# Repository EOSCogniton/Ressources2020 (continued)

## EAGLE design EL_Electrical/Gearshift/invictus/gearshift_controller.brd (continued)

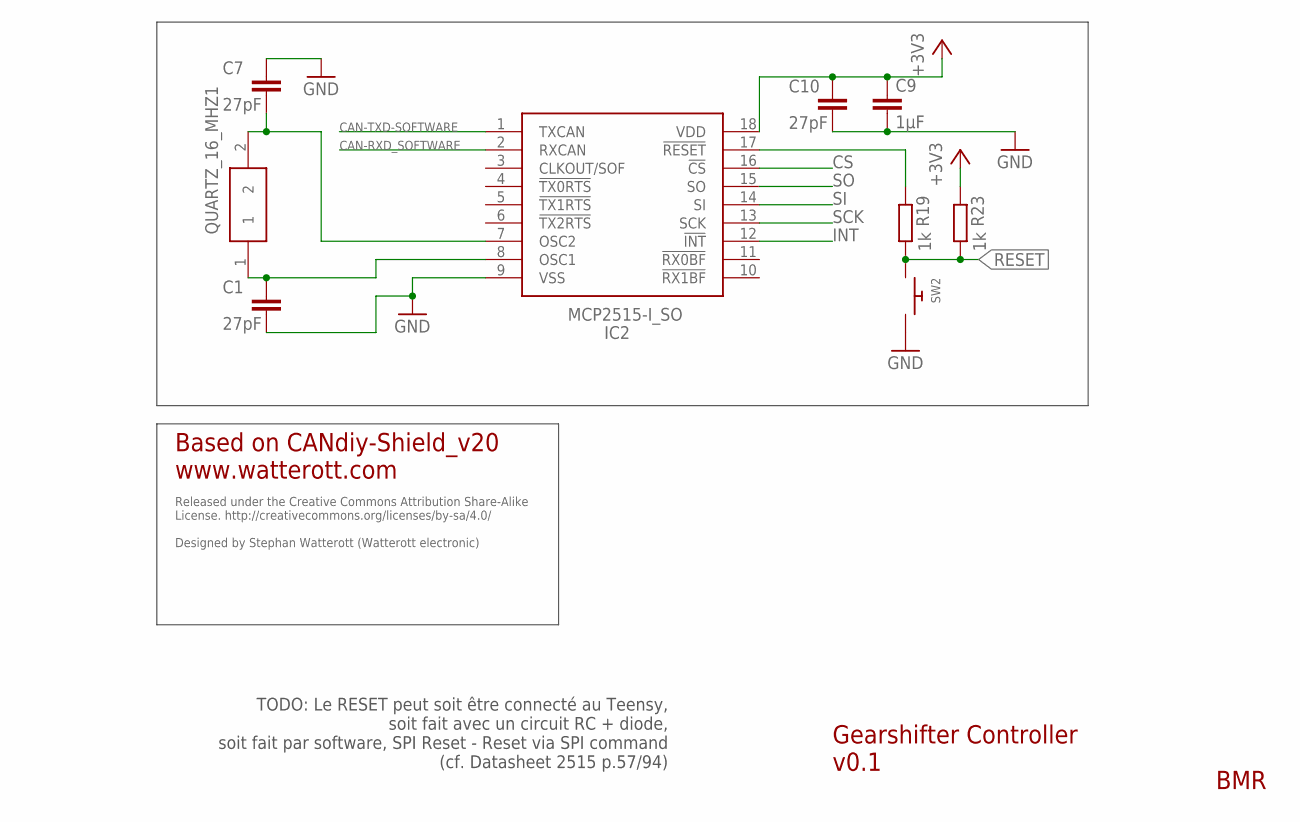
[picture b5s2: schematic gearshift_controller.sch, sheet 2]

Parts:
C1, C7, C10: 27pF; C0805
C9: 1µF; C0805
IC2: MCP2515-I_SO; SOIC127P1030X265-18N
QUARTZ_16_MHZ1: FOXSLF_160-20; HC49SLF_1
R19, R23: 1k; R0805
SW2: SWITCH_PUSHBUTTONEVQ-PE; TACT_PANA-EVQ

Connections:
+3V3: C9.1, C10.1, IC2.18 (VDD), R23.1; also elsewhere on the board
CAN-RXD_SOFTWARE: IC2.2 (RXCAN); also elsewhere on the board
CAN-TXD-SOFTWARE: IC2.1 (TXCAN); also elsewhere on the board
CS: IC2.16 (!CS); also elsewhere on the board
GND: C1.2, C7.1, C9.2, C10.2, IC2.9 (VSS), SW2.P$2; also elsewhere on the board
INT: IC2.12 (!INT); also elsewhere on the board
unnamed: C1.1, IC2.8 (OSC1), QUARTZ_16_MHZ1.1
unnamed: C7.2, IC2.7 (OSC2), QUARTZ_16_MHZ1.2
unnamed: IC2.17 (!RESET), R19.1
RESET: R19.2, R23.2, SW2.P$1
SCK: IC2.13 (SCK); also elsewhere on the board
SI: IC2.14 (SI); also elsewhere on the board
SO: IC2.15 (SO); also elsewhere on the board

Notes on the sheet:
Gearshifter Controller v0.1
BMR
Released under the Creative Commons Attribution Share-Alike License. http://creativecommons.org/licenses/by-sa/4.0/ Designed by Stephan Watterott (Watterott electronic)
Based on CANdiy-Shield_v20 www.watterott.com
TODO: Le RESET peut soit être connecté au Teensy, soit fait avec un circuit RC + diode, soit fait par software, SPI Reset - Reset via SPI command (cf. Datasheet 2515 p.57/94)

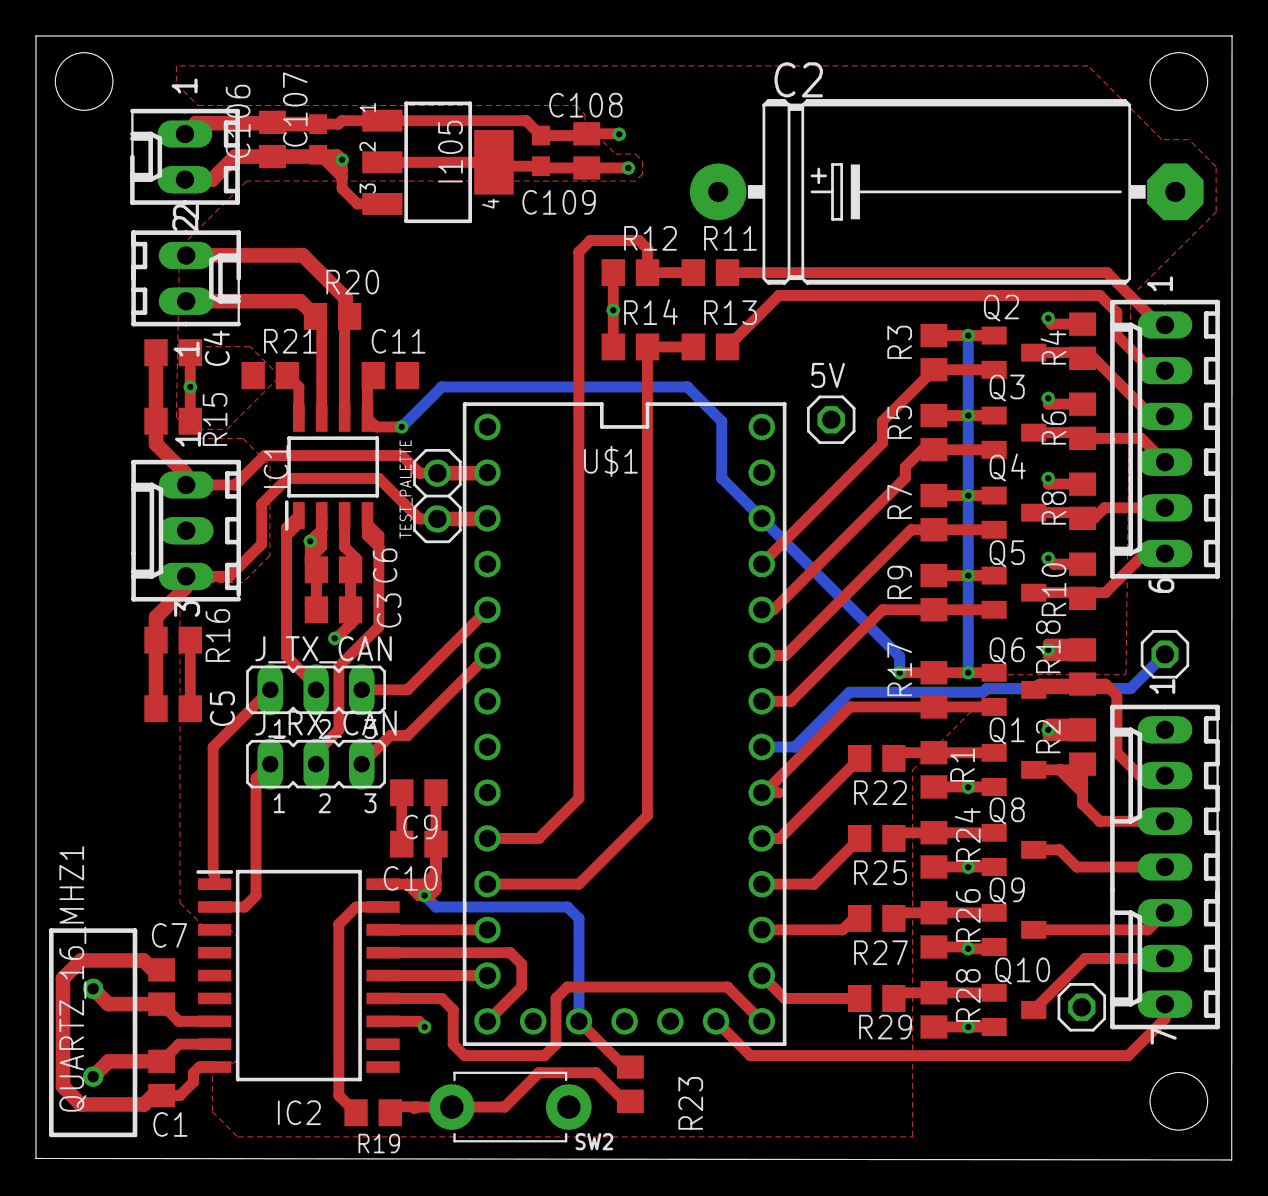
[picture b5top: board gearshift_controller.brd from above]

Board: 4 copper layers, 66.4 x 62.4 mm, 69 parts (0 on the bottom side), 52 nets.

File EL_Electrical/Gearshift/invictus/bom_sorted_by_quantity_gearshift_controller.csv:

"Qty";"Value";"Device";"Package";"Parts";"Description";"ALLIED_NUMBER";"CASE";"DESCRIPTION";"HEIGHT";"MANUFACTURER_NAME";"MANUFACTURER_PART_NUMBER";"MF";"MONTHLY_USAGE";"MPN";"OC_FARNELL";"OC_NEWARK";"PART_NUMBER";"POPULARITY";"PRICE";"RS_PART_NUMBER";"SPICEPREFIX";"SUPPLIER";"TYPE";"VALUE";
"2";"";"JP2E";"JP2";"JP1, JP2";"JUMPER";"";"";"";"";"";"";"";"";"";"";"";"";"34";"";"";"";"";"";"";
"1";"";"SWITCH_PUSHBUTTONEVQ-PE";"TACT_PANA-EVQ";"SW2";"Buttons";"";"";"";"";"";"";"";"";"";"";"";"";"";"";"";"";"";"";"";
"1";"0.1 µF";"C-EUC0805";"C0805";"C11";"CAPACITOR, European symbol";"";"";"";"";"";"";"";"";"";"";"";"";"88";"";"";"C";"";"";"";
"2";"0.33µF";"C-EUC0805";"C0805";"C4, C5";"CAPACITOR, European symbol";"";"";"";"";"";"";"";"";"";"";"";"";"88";"";"";"C";"";"";"";
"1";"1 µF";"C-EUC0805";"C0805";"C3";"CAPACITOR, European symbol";"";"";"";"";"";"";"";"";"";"";"";"";"88";"";"";"C";"";"";"";
"1";"100k";"R-EU_R0805";"R0805";"R21";"RESISTOR, European symbol";"";"";"";"";"";"";"";"";"";"";"";"";"86";"";"";"R";"";"";"";
"2";"100n";"C-EUC0603";"C0603";"C107, C109";"CAPACITOR, European symbol";"";"";"";"";"";"";"";"";"";"";"";"";"";"";"";"";"";"";"";
"16";"10k";"R-EU_R0805";"R0805";"R1, R3, R4, R5, R6, R7, R8, R9, R10, R15, R16, R17, R18, R24, R26, R28";"RESISTOR, European symbol";"";"";"";"";"";"";"";"";"";"";"";"";"86";"";"";"R";"";"";"";
"2";"10µ";"C-EUC0805";"C0805";"C106, C108";"CAPACITOR, European symbol";"";"";"";"";"";"";"";"";"";"";"";"";"88";"";"";"C";"";"";"";
"1";"120 ";"R-EU_R0805";"R0805";"R20";"RESISTOR, European symbol";"";"";"";"";"";"";"";"";"";"";"";"";"86";"";"";"R";"";"";"";
"2";"18k";"R-EU_R0805";"R0805";"R11, R13";"RESISTOR, European symbol";"";"";"";"";"";"";"";"";"";"";"";"";"86";"";"";"R";"";"";"";
"2";"1k";"R-EU_R0805";"R0805";"R19, R23";"RESISTOR, European symbol";"";"";"";"";"";"";"";"";"";"";"";"";"86";"";"";"R";"";"";"";
"1";"1µF";"C-EUC0805";"C0805";"C9";"CAPACITOR, European symbol";"";"";"";"";"";"";"";"";"";"";"";"";"88";"";"";"C";"";"";"";
"1";"22-05-7028-02";"22-05-7028-02";"7395-02";"ALIM";"CONNECTOR";"";"";"";"";"";"";"";"";"";"";"";"";"";"";"";"";"";"";"";
"1";"22-05-7028-02";"22-05-7028-02";"7395-02";"CONN_CAN";"CONNECTOR";"";"";"";"";"";"";"MOLEX";"";"";"9731601";"unknown";"";"0";"";"";"";"";"";"";
"1";"22-05-7038-03";"22-05-7038-03";"7395-03";"PALETTE";"CONNECTOR";"";"";"";"";"";"";"";"";"";"";"";"";"";"";"";"";"";"";"";
"1";"22-05-7068-06";"22-05-7068-06";"7395-06";"CONN_MOTOR";"CONNECTOR";"";"";"";"";"";"";"MOLEX";"";"";"unknown";"unknown";"";"0";"";"";"";"";"";"";
"1";"22-05-7078-07";"22-05-7078-07";"7395-07";"CONN_DTA";"CONNECTOR";"";"";"";"";"";"";"MOLEX";"";"";"unknown";"unknown";"";"0";"";"";"";"";"";"";
"4";"27pF";"C-EUC0805";"C0805";"C1, C6, C7, C10";"CAPACITOR, European symbol";"";"";"";"";"";"";"";"";"";"";"";"";"88";"";"";"C";"";"";"";
"4";"330";"R-EU_R0805";"R0805";"R22, R25, R27, R29";"RESISTOR, European symbol";"";"";"";"";"";"";"";"";"";"";"";"";"86";"";"";"R";"";"";"";
"1";"4k7";"R-EU_R0805";"R0805";"R2";"RESISTOR, European symbol";"";"";"";"";"";"";"";"";"";"";"";"";"86";"";"";"R";"";"";"";
"2";"6k8";"R-EU_R0805";"R0805";"R12, R14";"RESISTOR, European symbol";"";"";"";"";"";"";"";"";"";"";"";"";"86";"";"";"R";"";"";"";
"9";"BSS138";"BSS123";"SOT23";"Q1, Q2, Q3, Q4, Q5, Q6, Q8, Q9, Q10";"N-CHANNEL MOS FET";"";"";"";"";"";"";"";"";"";"";"";"";"21";"";"";"";"";"";"";
"1";"FOXSLF_160-20";"FOXSLF_160-20";"HC49SLF_1";"QUARTZ_16_MHZ1";"Crystal 16.000MHz HC49S HC-49-SLF Crystal 16MHz, ??30ppm, 2-Pin";"";"";"Crystal 16.000MHz HC49S HC-49-SLF Crystal 16MHz, ??30ppm, 2-Pin";"mm";"Fox";"FOXSLF/160-20";"";"";"";"";"";"";"";"";"1734298";"";"";"";"";
"1";"LM1117MPX-5.0";"0022_LM1117IMPX-5.0";"LINEAR_SOT223";"I105";"Low-dropout linear regulator 5V  -LM1117IMPX-5.0";"";"SOT223";"";"";"";"";"";"_____";"";"";"";"LM1117IMPX-5.0";"";"_____";"";"";"_____";"Circuito_Integrato";"LM1117IMPX-5.0";
"1";"MCP2515-I_SO";"MCP2515-I_SO";"SOIC127P1030X265-18N";"IC2";"CAN Controller SPI data filtering SO18";"70045399";"";"CAN Controller SPI data filtering SO18";"2.65mm";"Microchip";"MCP2515-I/SO";"";"";"";"";"";"";"";"";"1445765";"";"";"";"";
"1";"MCP2562-E_SN";"MCP2562-E_SN";"SOIC127P600X175-8N";"IC1";"CAN Transceiver 1Mbps 5V 125degC SOIC8 CAN Transceiver 1MBps IEC 61000-4-2 Standby-Mode 8pins SOIC";"70415107";"";"CAN Transceiver 1Mbps 5V 125degC SOIC8 CAN Transceiver 1MBps IEC 61000-4-2 Standby-Mode 8pins SOIC";"1.75mm";"Microchip";"MCP2562-E/SN";"";"";"";"";"";"";"";"";"7990228P";"";"";"";"";
"1";"TEENSY_3.1-3.2_OUTER_ROW";"TEENSY_3.1-3.2_OUTER_ROW";"TEENSY_3.0-3.2&LC_OUTER_ROW";"U$1";"Footprint for Teensy 3.1 or 3.2 board using all pin connections on the outer perimeter";"";"";"";"";"";"";"";"";"";"";"";"";"";"";"";"";"";"";"";

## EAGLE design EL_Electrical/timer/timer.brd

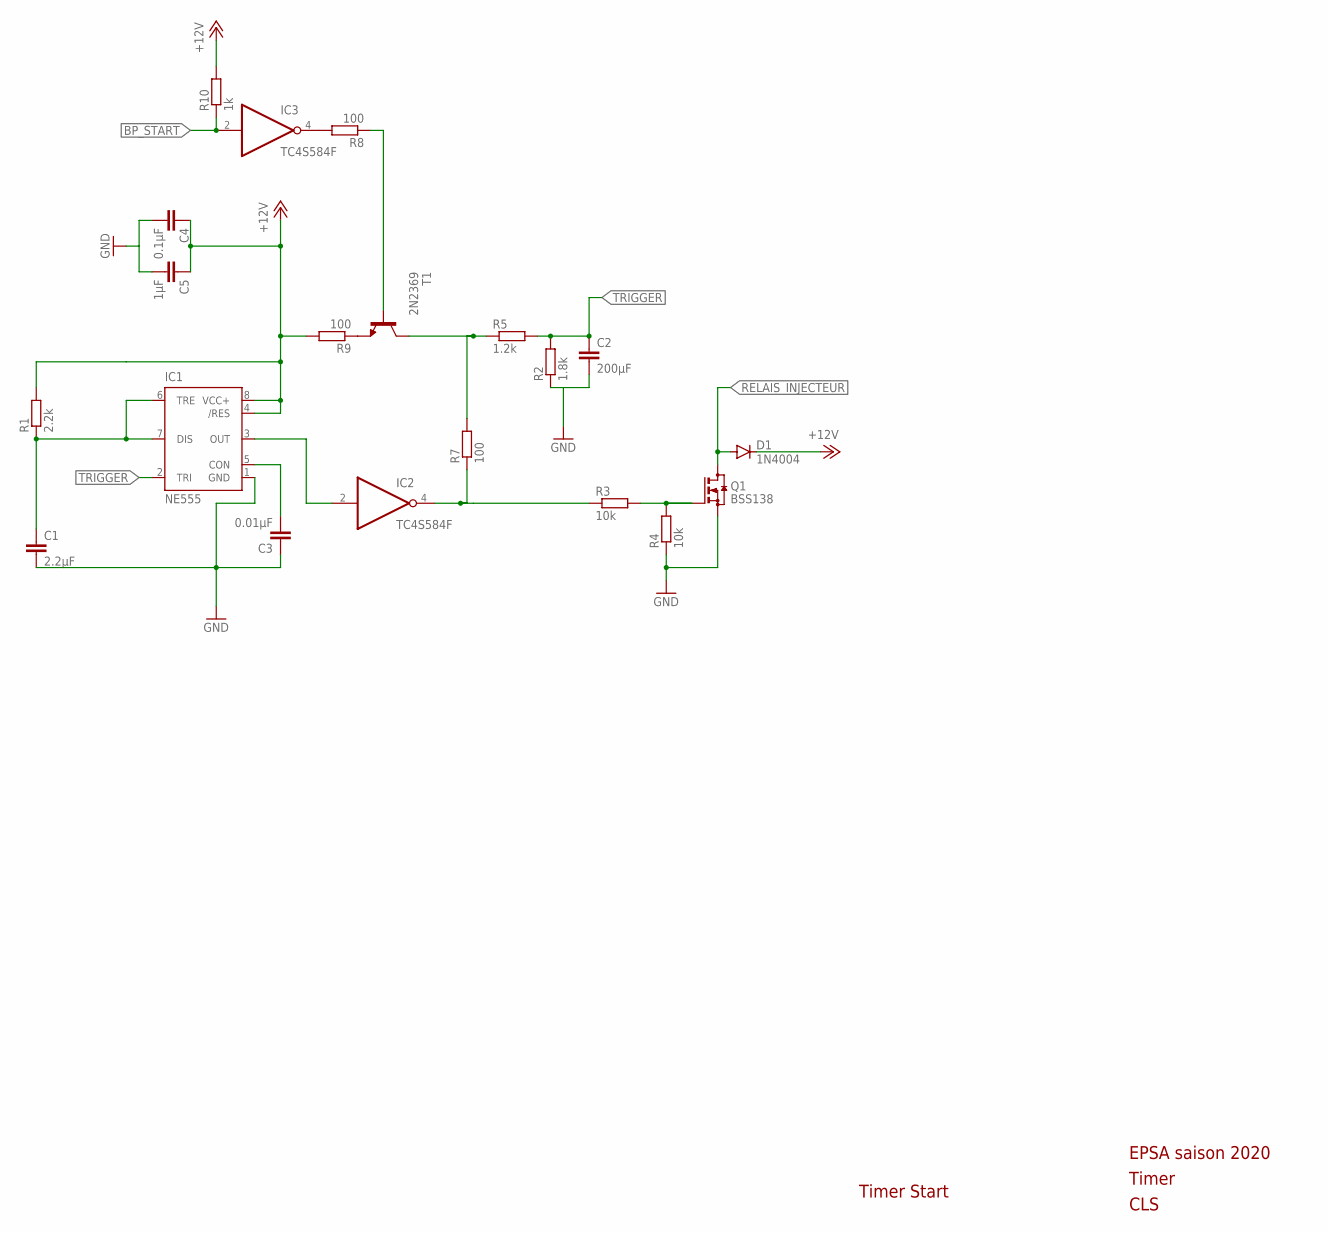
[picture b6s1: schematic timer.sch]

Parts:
C1: 2.2µF; C0805
C2: 200µF; C0805
C3: 0.01µF; C0805
C4: 0.1µF; C0805
C5: 1µF; C0805
D1: 1N4004; DO41-10
IC1: NE555; DIL-08
IC2, IC3: TC4S584F; SOT23-5
Q1: BSS138; SOT23
R1: 2.2k; R0805
R2: 1.8k; R0805
R3, R4: 10k; R0805
R5: 1.2k; R0805
R7, R8, R9: 100; R0805
R10: 1k; R0805
T1: 2N2369; TO18

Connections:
+12V: C4.1, C5.1, D1.C, IC1.4 (/RES), IC1.8 (VCC+), R1.2, R9.2, R10.2
BP_START: IC3.2 (I), R10.1
GND: C1.2, C3.1, IC1.1 (GND), IC2.3 (GND), IC3.3 (GND), Q1.2 (S), R4.1
unnamed: C3.2, IC1.5 (CON)
unnamed: C1.1, IC1.6 (TRE), IC1.7 (DIS), R1.1
unnamed: C4.2, C5.2
unnamed: C2.2, R2.1
unnamed: R5.1, R7.2, T1.3 (C)
unnamed: IC2.4 (O), R3.1, R7.1
unnamed: Q1.1 (G), R3.2, R4.2
unnamed: IC1.3 (OUT), IC2.2 (I)
unnamed: IC3.4 (O), R8.2
unnamed: R9.1, T1.1 (E)
unnamed: R8.1, T1.2 (B)
RELAIS_INJECTEUR: D1.A, Q1.3 (D)
TRIGGER: C2.1, IC1.2 (TRI), R2.2, R5.2
VCC: IC2.5 (VCC), IC3.5 (VCC)

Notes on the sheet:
Timer Start
EPSA saison 2020
CLS
Timer

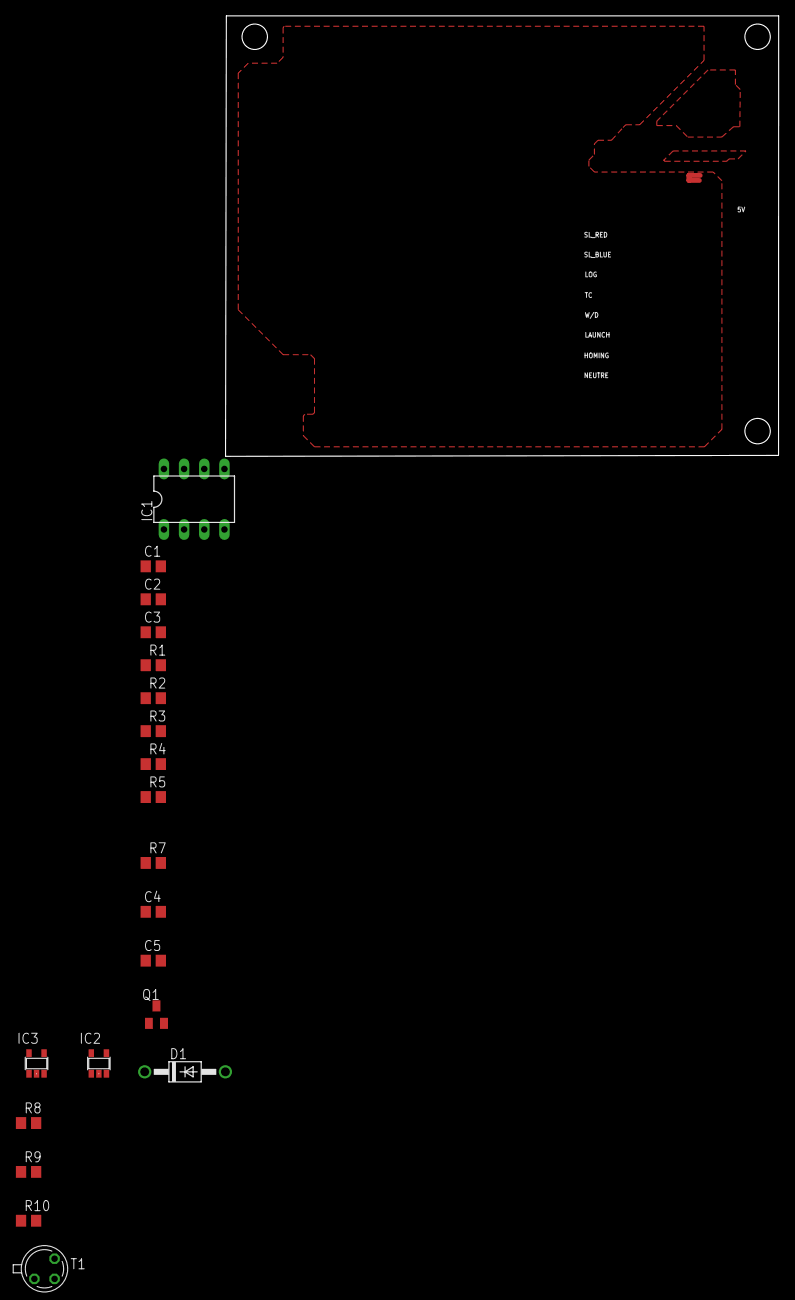
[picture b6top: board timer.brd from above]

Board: 4 copper layers, 69.6 x 55.5 mm, 20 parts (0 on the bottom side), 17 nets.

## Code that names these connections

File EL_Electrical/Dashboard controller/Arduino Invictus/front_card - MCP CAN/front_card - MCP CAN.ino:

/***************************************************************
  @file: front_card
  @author: Raphaël Viudès(RVS)
     for Ecurie Piston Sport Auto
      at Ecole Centrale de Lyon
  @description: countains the main program which picks up CAN data and updates the screen display
  @functions: setup()
                      Initiates ports and displays
              loop()
                      Does all the screen display process
                    
****************************************************************/
#include "nextion_communication_v2.h"
#include "projectconfig.h"
#include "can_interface.h"
#include <stdio.h>
#include <SPI.h>
#include <mcp_can.h>
#include <mcp_can_dfs.h>


int ancgear;
int nvgear;
int nvpage;
int ancpage;
boolean changementPage;
char vitesse[7]={'N','1','2','3','4','5','6'};
bool anclaunch;
bool nvlaunch;
bool ancrace;
bool nvrace;
unsigned long TchgtPage;

int rpm_old=0;
int rpm_new=0;
int drpm=0;
int seuildrpm=100;
float dt=0.05;
int min1Rpm=11500;
int min2Rpm=12000;

int homing, neutre,log_DTA, TC_control, launch_control, Wet_ON;

//Initialization of CANBUS
can_interface CAN;
IntervalTimer CANTimer;
unsigned long Can_send_period=75000; //On envoie sur le can toutes les 75ms
//header des fonctions
void Can_Send();
void setRPMShiftLight(int RPM);

void setup() {
  //définition des entrées-sorties
  pinMode(Neutre_button,INPUT_PULLUP);
  pinMode(Homing_button,INPUT_PULLUP);
  pinMode(LaunchControl_button,INPUT_PULLUP);
  pinMode(WD_Switch,INPUT_PULLUP);
  pinMode(TC_Switch,INPUT_PULLUP);
  pinMode(Log_switch,INPUT_PULLUP);
  pinMode(RED_SHIFT_PIN,OUTPUT);
  pinMode(BLUE_SHIFT_PIN,OUTPUT);
  
  pinMode(13,OUTPUT);
  digitalWrite(13,HIGH);
  //Initialisation of the variables used in the program
  homing=1;
  neutre=1;
  log_DTA=1;
  TC_control=1;
  launch_control=1;
  Wet_ON=1;
  
  //nvvalue is for the new value of value
  //which is compared to its prec value, ancvalue
  //in order to save screen loading times 
  ancgear=0;
  ancpage=1;
  nvpage=1;
  TchgtPage=0;
  changementPage=false;
  anclaunch=false;
  nvlaunch=false;
  ancrace=false;
  nvrace=false;
  
  Serial2.begin(9600);
  Serial.begin(9600);

  
  //Start display
  //Puts on the lights for 2 seconds and displays welcome page on screen
  Serial2.print("page ");
  Serial2.print(0);
  nextion_endMessage();
  digitalWrite(BLUE_SHIFT_PIN,HIGH);
  digitalWrite(RED_SHIFT_PIN,HIGH);
  //Voir avec Bruno pour la commande d'affichage lumineux des boutons
  delay(2000);
  //Sets the screen at its work state
  Serial2.print("page ");
  Serial2.print(1);
  nextion_endMessage();
  digitalWrite(BLUE_SHIFT_PIN,LOW);
  digitalWrite(RED_SHIFT_PIN,LOW);
  
  //Can et interruption
  //Define Timer
  CANTimer.begin(Can_Send, Can_send_period); //each period of the Timer the function Can_Send is launched
}

void loop() {
  CAN.Recieve();
  homing=digitalRead(Homing_button);
  neutre=digitalRead(Neutre_button);
  log_DTA=digitalRead(Log_switch);
  TC_control=digitalRead(TC_Switch);
  launch_control=digitalRead(LaunchControl_button);
  Wet_ON=digitalRead(WD_Switch);

  if ( !homing)
  {
    Serial.println("appui homing");
  }
  if ( !neutre)
  {
    Serial.println("appui neutre");
  }
  if(!log_DTA)
  {
    Serial.println("log dta activé");
  }
  if(!TC_control)
  {
    Serial.println("TC_control activé");
  }
  if(!launch_control)
  {
    Serial.println("launch_control activé");
  }
  if(!Wet_ON)
  {
    Serial.println("Wet_ON activé");
  }
  
  //Shift light :on allume en fonction des rpms pour savoir si on change de vitesse
  setRPMShiftLight(CAN.RPM);
  
  //This part is for a button which swaps between pages
  changementPage=digitalRead(Chgt_screen_button)*true; //Quand on appuie sur l'écran ou le bouton ( à voir car il n'y a pas de connexion avec le bouton) il faut changer de page;
  TchgtPage=millis()-TchgtPage;
  if(changementPage && TchgtPage>500) //On regarde si cela fait plus de 500ms qu'on a voulu changer de page (Permet d'éviter le fait qu'on est plusieurs loop avec changementPage qui reste à 1 alors que c'est le même appui)
  {
    if(ancpage==2)
    {
      nvpage=1;
    }
    else
    {
      nvpage=ancpage+1;
    }
    changePage(nvpage);
    ancpage=nvpage;
    updateDisplay(nvpage,CAN.gear,CAN.oilPressure,CAN.Volts,CAN.RPM,nvlaunch);
  }
  if(CAN.gear!=ancgear){//Changing gear
    ancgear=CAN.gear;
    setGear(vitesse[nvgear]);
  }
  if(nvrace!=ancrace){//Changing race capture activation state
    ancrace=nvrace;
    setRaceCapture(nvrace);
  }
  if(nvlaunch!=anclaunch){
    anclaunch=nvlaunch;
    setLaunch(ancpage,nvlaunch);
  }
  setWaterTemp(CAN.waterTemp);
  setVoltage(CAN.Volts);
  setRPM(CAN.RPM);
  setOil(CAN.oilPressure,CAN.RPM);
  setThrottle(CAN.throttle);
  setPlenum(CAN.plenum);
  setLambda(CAN.Lambda);
}

void setRPMShiftLight(int RPM)
{
  rpm_old=rpm_new;
  rpm_new=RPM;
  drpm=abs(rpm_new-rpm_old)/dt;
  if(drpm>seuildrpm){
    Serial2.print("problem.txt=rpm");
  }
  if(RPM<min1Rpm) //min1Rpm=11500; min2Rpm=12000
  {
    digitalWrite(BLUE_SHIFT_PIN,LOW);
    digitalWrite(RED_SHIFT_PIN,LOW);
  } else if( RPM<min2Rpm)
  {
    digitalWrite(BLUE_SHIFT_PIN,HIGH);
    digitalWrite(RED_SHIFT_PIN,LOW);
  } else{
    digitalWrite(BLUE_SHIFT_PIN,HIGH);
    digitalWrite(RED_SHIFT_PIN,HIGH);
  }
}

void Can_Send()
{
  CAN.Transmit(homing, neutre,log_DTA, TC_control, launch_control, Wet_ON);
}

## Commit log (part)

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2019-07-14 Rangement STUF
2019-07-14 Gantt / Mail
2019-08-24 Gantt
2019-09-03 Gantt et formations
2019-09-05 CR et Gantt
2019-09-20 GANTT et PE
2019-09-20 Archive GANTT
2019-09-22 Gantt - Mail - Salle
2019-09-22 DM Caria
2019-09-22 Mail
2019-09-26 Formation et Mail
2019-10-01 Rangement
2019-10-01 Management
2019-10-01 Règles rangement
2019-10-01 Ajout elec non catia
2019-10-02 Ajout Modèles + Preliminary
2019-10-02 Liste de diffusion
2019-10-02 modèles suspension et courbes pneus et amortisseurs
2019-10-02 MAJ architecture faisceau
2019-10-04 COMSOL
2019-10-04 Ajout tutos catia electrical
2019-10-08 add info passage de vitesse
2019-10-08 Tout
2019-10-08 suivi carte avant
2019-10-08 Contenu TOP Synthese
2019-10-09 Premier jet design affichage écran
2019-10-09 Salle_TS
2019-10-09 Dash Optimus
2019-10-09 Dash_Pcars_ARZ
    Exemple code dash
2019-10-09 Modifs mineures conversion hexa/deci CAN
2019-10-10 Template + Odj TS
2019-10-10 Template TS
2019-10-10 Audit Volvo
2019-10-11 Maj Diapo Volvo
2019-10-11 Delete Dashboard Optimus
    Arthur il y a STUF-2019 pour ça
2019-10-11 MG_Mail_Gantt
2019-10-12 Add documentation (MCP2515.pdf, MCP2562.pdf, TB3101-MCP2551 to MCP2561 Migration.pdf and pins diagram for Teensy 3.1 and 3.2)
2019-10-12 Add v0.1 gearshift_controler (Eagle files) and file to organize infos from CAN Transceivers devices compatibles with Teensy 3.2
2019-10-13 ajout doc boite à fusible avant
2019-10-13 ajout modèles
2019-10-14 modèles tjrs
2019-10-14 aimery le zgeg
2019-10-15 cyshu la pougne
2019-10-16 Budget hH
2019-10-16 Ajout pages écran + création programme affichage
2019-10-16 Supression images inutiles écran
2019-10-16 Scrum meeting
2019-10-16 Ecriture programme affichage écran + nouvelles pages d'affichage et màj design
2019-10-16 Update of electrical schematic (4 pins from DTA extras)
2019-10-17 réorganisation
2019-10-21 Formation CM 4
2019-10-21 Rangement + Listes 0A / 2A
2019-10-22 Point projet
2019-10-22 Carnet conception
2019-10-23 Création fichiers h et cpp Nextion et Shiftlight + PinMap
2019-10-24 Definition of inputs/outputs in Teensy 3.2. PCB Layout Design (ground plane missing)
2019-10-24 model
2019-10-24 carnet de conception
2019-10-24 Gantt seism
2019-10-24 Modifs mineures logo epsa écran
2019-10-24 gantt LAS pas fini
2019-10-24 matériaux
2019-10-24 Update de sch et brd files (Position of connectors, minor changes)
2019-10-27 Gantt motorisation + chassis équipé
2019-10-27 doc boîte à fusible
2019-10-29 Update gantt
2019-10-31 Recap Bus CAN
2019-11-02 gantt LAS and gantt2latex visualization
2019-11-02 maj gantt LAS et gant2latex, tutor pour le BOM et les Devis
2019-11-03 Gantt motorisation
2019-11-04 maj gantt LAS v03
2019-11-05 Gant motorisation + Point projet
2019-11-05 Fichier install Ganttproject
2019-11-05 Maj Gantt
2019-11-05 Suivi dashboard
2019-11-05 Carnet de conception
    Correction coquilles
2019-11-05 Add Bill of Materials (BOM) of gearshift_controller PCB without pinheaders for test points. Minor changes in names
2019-11-05 modif pour commande
2019-11-05 Gantt chassis
2019-11-05 faisceau V0.6
2019-11-05 Add test pins
2019-11-05 Motorisation, again and again
2019-11-06 Bus_CAN et Steering_Wheel_Adapter
2019-11-07 Motorisation + Point projet
2019-11-07 gant elec
2019-11-08 Replace pin test
2019-11-08 Cellule chrono
2019-11-08 Ajout début tuto faisceau sous CATIA
2019-11-11 Cell chromo scheme
2019-11-11 Contenu Audit Technique
2019-11-12 Ground plane for gearshift. Add dashboard
2019-11-12 Minor changes and missing connection fixed in Dashboard_controller
2019-11-12 Cell chrono + timer
2019-11-14 Template audit
2019-11-14 Audit
2019-11-14 Chrono cell
2019-11-15 Contenu audit
2019-11-16 Gearshift_controller schematic file (.sch) updade
2019-11-16 Change circuit to drive the shift LEDs and Launch Control button
    TODO: (re)change pin order to shorten 3.3V route (botton layer) and top layers route
    TODO 2: add big capacitor
2019-11-17 Partie 2 tuto elec Catia
2019-11-19 Annotation du code
2019-11-20 Racecapture
2019-11-20 Ajout nouvelles sorties
2019-11-20 Màj prog carte avant fonctionnel
2019-11-20 Cell chrono
2019-11-20 Oubli lors ajout RaceCapture affichage
2019-11-22 Prog carte avant finalisé (manque acquisition CAN)
2019-11-22 Screen_Display
2019-11-22 Screen_Display_2
2019-11-22 Add capacitors (470uF: about 18,20mm x 10,8mm; Footprint utilisé 25mm x 10mm)
2019-11-22 Modif Mineures
2019-11-22 Nouveau programme FlexCAN
2019-11-22 Programme Carte avant FlexCAN
2019-11-22 Library FlexCAN
2019-11-24 SU maj raideur suspension + BAR
2019-11-25 Ecran avec pictos
2019-11-27 Ecran launch control et RaceCat màj affichage
2019-11-27 Ménage et adaptation du code 2019 à 2020
2019-11-27 Ajout voyant pression d'huile écran
2019-11-28 Add neutral sensor connector (to use with Teensy's pull-up resistors), delete uselless dta test pins
2019-11-29 Tutos de Frame&Body
2019-11-29 timer, faisceau, boite
2019-11-30 Ajout page contrôleurs moteur et pictogrammes pb moteur
2019-12-02 ajout matériaux
2019-12-02 Dossier GMP
2019-12-03 ajout memento technique
2019-12-03 Change connector footprint, LDO regulator (DC linear voltage regulator) position and reduce the size
2019-12-03 Change connector footprint, LDO regulator (DC linear voltage regulator) position and reduce the size for Gearshift Controller pcb Reduce 1mm for Dashboard Controller pcb
2019-12-03 modif boite
2019-12-04 ajout boite excel
2019-12-04 bom carte arrière
2019-12-04 cartos vulcanix
2019-12-04 Bom des cartes
2019-12-04 aimery trop fouqué
2019-12-06 Increase readability of values (gearshift_controller)
2019-12-07 Increase readability of values (dashboard_controller)
2019-12-08 Diapos Top Copeau
2019-12-10 Connecteurs
2019-12-10 Beging of Timer_controller PCB
2019-12-10 comp. carte
2019-12-10 relecture carte et suivi
2019-12-10 maj faisceau
2019-12-11 Porte clé
2019-12-11 Update sch and PCB (Timer Controller)
2019-12-11 Ménage
2019-12-11 Code carte gearshift
2019-12-11 Modif code gearshift
2019-12-11 Update holes and text
2019-12-13 SU update calcul ARB
2019-12-15 SU maj raideur ARB
2019-12-16 Add text with informations (PCB and car names) to PCB
2019-12-16 maj connecteurs
2019-12-17 Connecteur boite elec
2019-12-17 correction_final carte + fichier prod Cirly
2019-12-18 Màj design affichage écran
2019-12-18 Up sur le code optimus gearshift
2019-12-19 Update Timer t=2s de pause
2019-12-19 maj timer
2020-01-06 simul matlab timer
2020-01-07 Update timer_controller
2020-01-07 maj composant
2020-01-10 Debut commande
2020-01-10 Change footprint for 150uF capacitor. Rearrange text infos. Add a GND test pin
2020-01-10 C 150uF Farnell
2020-01-14 Timer_controller add pin
2020-01-18 Ajout plan faisceau avant
2020-01-28 Diapo
2020-01-28 Update with Farnell links (last tab "Quant__Composant")
2020-01-29 Update with Farnell links (last tab "Quant__Composant") from Google Sheet Commandes - Invictus 2019 and "supports à coller pour faisceau chez RS"
2020-01-29 Commande-janvier with several itens (and their links)
2020-01-29 maj tableau commande
2020-02-05 Pression et discontinuité valeurs écran
2020-02-12 Modif fichier can_interface
2020-02-12 Discontinuité grandeurs écran (manque les seuils)
2020-02-12 CC_Cell_Chrono
2020-02-15 Ajout commande Mouser à l'excel de commande
2020-02-18 exxe
2020-02-18 add commande février
2020-02-18 Ajout connections RaceCapture
2020-02-19 Modif code carte arrière
2020-02-20 maj commande Mouser après vérifs Bron
2020-02-21 ajout antenne GPS aux commandes
2020-02-22 Schéma boîte à fusible
2020-02-23 CC_Box
2020-02-23 CC_Catia
2020-02-27 Pour Michele
2020-03-01 Rangements cartos
2020-03-04 CC_Chrono
2020-03-08 SU kit de montage
2020-03-08 MEP faisceau arrière
2020-03-10 Update Comande-février Reverchon
2020-03-10 Update Commande-février
2020-03-10 correction bug format tableau commande
2020-03-11 MAJ du code gearshift
2020-03-17 laj connecteur
2020-03-19 LapTime commentaire dynamique véhicule
2020-03-20 LapTime fix nomenclature
    g is still a parameter
2020-03-20 PROMs / PROCs bouillons
2020-03-21 Laptime MF
2020-03-21 LapTime maj parametrage
2020-03-21 LapTime maj commentaires
2020-03-21 formule pneu pour calcul matriciel
2020-03-21 LapTime simplified magin formula 2
    ne pas terminé
2020-03-22 LapTime tire model & optimum verification script
2020-03-22 update findGymax
    ajoute nouveau aramètre charge nominale dans le modèle du pneu
2020-03-22 LapTime update structure dossiers et doc
2020-03-22 code ok pour version michele + rangement
2020-03-22 LapTime première version doc laterale
2020-03-22 LapTime lecture script accel
2020-03-22 Upload modèle conso essence
2020-03-22 doc simu globale
2020-03-26 Doc globale
2020-03-28 Simplification et commentaire code Laptime
2020-03-28 prise en compte répartition avant/arrière aéro
2020-03-28 LapTime maj schema accel
2020-03-28 COST passation
2020-03-28 LapTime maj accel pour GGV
2020-03-28 git ignore fichier .asv
2020-03-28 Ajout Braking
2020-03-29 Utilisation de braking dans LapTime
2020-04-05 Laptime fonctions calculs des points
    Accel, skid, autoc
2020-04-11 ajout aclaulc de point et maj interface
2020-04-20 carto invictus
2020-04-20 Carto invictus v1
2020-04-25 MAJ carto invictus
2020-04-27 Maj carto Invictus
    Ignition MAP
2020-04-27 maj dwell time
2020-04-28 Lancement COST
2020-04-29 maj TOC cost
2020-05-02 COST maj structure latex BOM
2020-05-05 COST maj AE
2020-05-08 LapTime elec
2020-05-19 Calcul de puissance élec ok Accel et skidpad à recaler sur Optimus
2020-05-24 Appli Fonctionelle + scripts de sensibilité
2020-05-24 oups
2020-06-11 doc VV
2020-06-22 PROM soudure et collage
2020-07-05 Notice Drexler
2020-07-07 powerbox
2020-07-15 excel connections faisceau
2020-07-15 code carte arrière avec interruptions et maj excel adress CAN
2020-07-25 MAJ carte avant correction bug et changement CAN
2020-07-26 maj code carte arrière
2020-07-26 finition code carte avant avant test
2020-07-30 modif carte avant pour test
2020-08-03 code carte avec MCP CAN
2020-09-10 Debug Can gearshift
2020-09-11 Debug code avant/arrière pour le CAN
2020-09-14 Test can écran + boutons
2020-09-23 carto atomix et dynamix
2020-10-05 maj excel integration faisceau
2020-10-07 maj excel intégration
2020-10-18 maj excel connection
2020-12-15 MAJ chainshield
2020-12-16 maj du plan
2020-12-16 maj du chainshield
2020-12-16 chainshield dxf
    fichier dxf pour decoup laser et plans de pliage/roulage
2021-01-05 maj plans chainshield
2021-01-06 plans chainshield de MKI
2021-01-06 maj chape chainshield
2021-01-06 maj chainshield production
2021-02-02 Carto banc givors
2021-02-02 push log 1er run invictus
2021-02-14 Debug code avant / arrière
2021-03-05 upload log DTA banc moteur
2021-03-05 MAP Invictus v3.0
2021-03-06 upload plots banc moteur
2021-03-08 Carto préliminaire
2021-03-16 je sais plus mais ça a changé
2021-03-24 deplacement données dans test-data
2021-03-27 MAP v3.2
2021-03-28 Problème can 5 minutes
2021-04-01 Tentative Log RC sur ecran
2021-04-11 Test problème timer
2021-04-15 Bom des PCB
2021-04-30 Carto 3e session banc moteur
2021-05-01 carto trou à 2000tr
2021-05-04 preset racecature
2021-05-04 idem
2021-05-07 Circuit Timer
2021-05-21 Timer
2021-05-25 Branchement bouton écran
2021-05-29 Maj connection log button
2021-06-05 Update code carte avant pour le changement d'ecran
2021-06-07 MAJ carto démarrage
2021-06-07 Preset Racecapture
2021-06-07 re preset RC
2021-06-11 modif timer
2021-06-12 MAJ Racecapture
2021-06-12 passage de vitesse automatique
2021-06-12 affichage log dta sur ecran
2021-06-16 Geometrie
2021-06-17 maj geometrie
2021-06-17 Mini maj carto
2021-06-17 Geometrie (foireuse), passage de vitesse auto et neutre
2021-06-17 Save RC
2021-06-18 Timer - production files
2021-06-19 Map ralenti
2021-06-20 Reglage DTA
2021-06-25 MAJ RPM passage vitesse auto + carto timer et nouveau TPS
2021-06-30 Update front_card-MCPCAN.ino
    RPM shiftlight en fonction du rapport engage
2021-06-30 Carto compete !!!!
2021-07-01 Correction shiftlight
    Modif shiftlight
2021-07-04 modif pour test shiftlight au neutre
2021-07-04 connection BSPD
2021-07-16 Suspension
2021-08-09 Preset Racecapture Invictus
2022-10-05 Formation Catia 0A
2022-11-20 dernieres cartos en date (FSG ?)
2022-12-03 courbes puissance moteur
